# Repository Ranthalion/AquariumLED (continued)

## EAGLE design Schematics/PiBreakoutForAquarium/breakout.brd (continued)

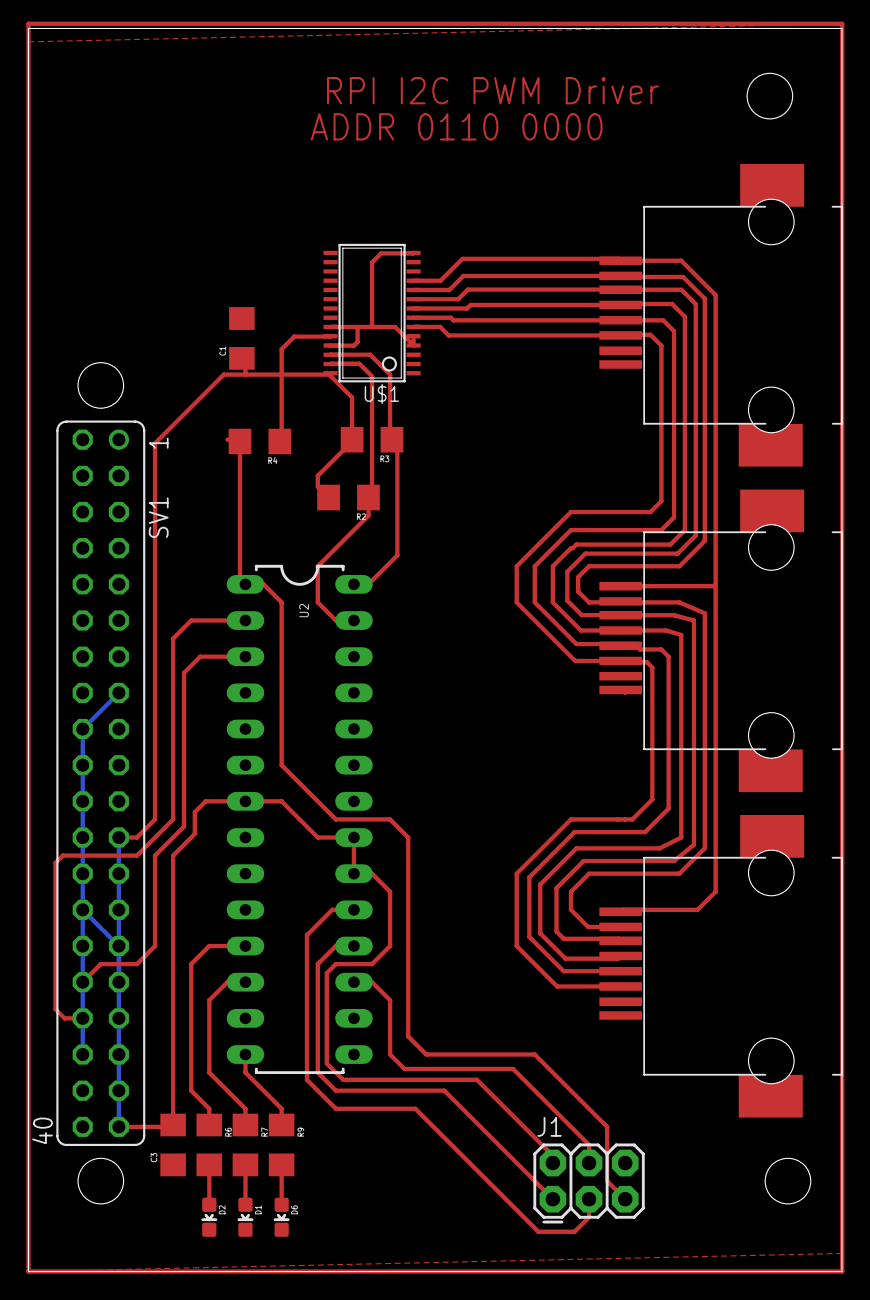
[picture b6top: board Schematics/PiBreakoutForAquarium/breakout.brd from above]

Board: 2 copper layers, 57.1 x 87.3 mm, 18 parts (0 on the bottom side), 22 nets.

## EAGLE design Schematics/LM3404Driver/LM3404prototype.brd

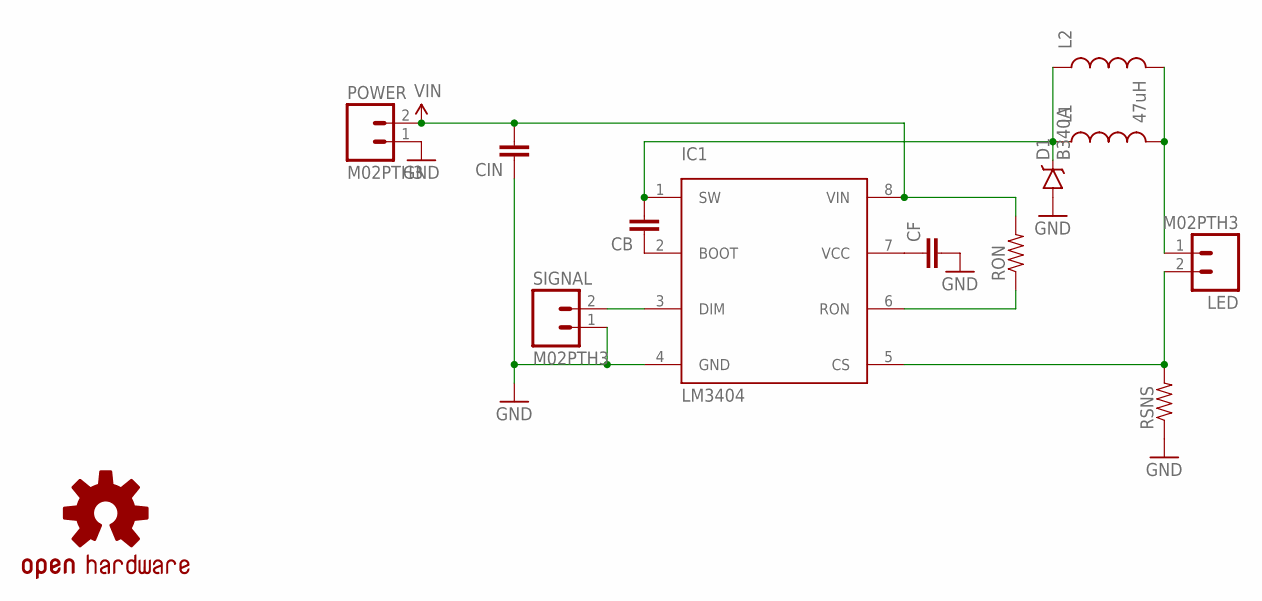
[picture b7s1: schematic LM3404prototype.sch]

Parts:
CB: CAP1206; 1206
CF: CAP1206; 1206
CIN: CAP1206; 1206
D1: B340A; SMA-DIODE
IC1: LM3404; SO8
L1: 47uH; CR75
L2: INDUCTORSDR1105; B82462G
LED: M02PTH3; 1X02_LONGPADS
LOGO1: OSHW-LOGOS; OSHW-LOGO-S
POWER: M02PTH3; 1X02_LONGPADS
RON: RESISTOR1206; 1206
RSNS: RESISTOR1206; 1206
SIGNAL: M02PTH3; 1X02_LONGPADS

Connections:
GND: CF.2, CIN.1, D1.A, IC1.4 (GND), POWER.1, RSNS.1, SIGNAL.1
unnamed: CF.1, IC1.7 (VCC)
unnamed: CB.1, IC1.2 (BOOT)
unnamed: CB.2, D1.C, IC1.1 (SW), L1.P$1 (1), L2.P$1 (1)
unnamed: IC1.5 (CS), LED.2, RSNS.2
unnamed: IC1.6 (RON), RON.1
unnamed: IC1.3 (DIM), SIGNAL.2
unnamed: L1.P$2 (2), L2.P$2 (2), LED.1
VIN: CIN.2, IC1.8 (VIN), POWER.2, RON.2

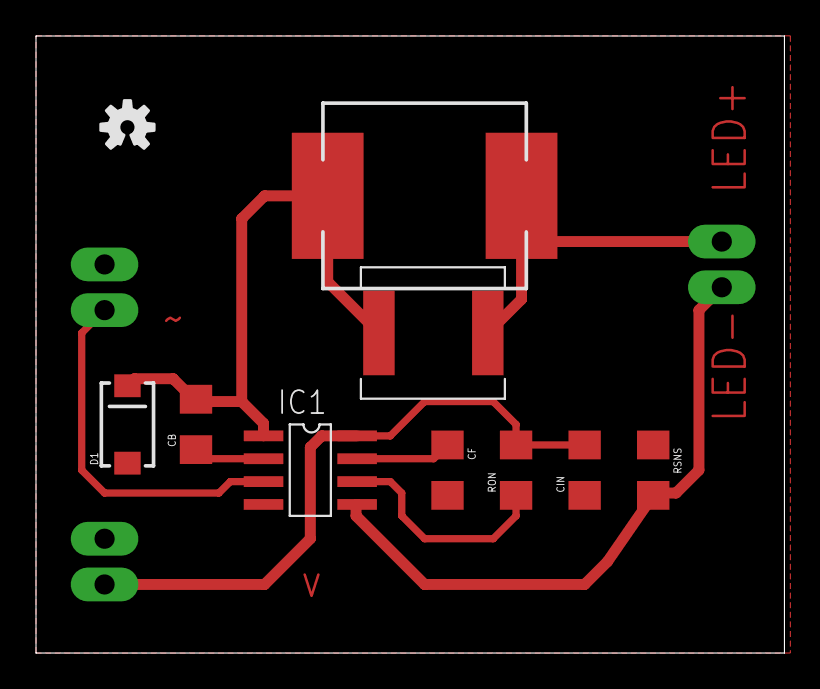
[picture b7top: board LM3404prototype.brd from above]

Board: 2 copper layers, 41.6 x 34.3 mm, 13 parts (0 on the bottom side), 9 nets.

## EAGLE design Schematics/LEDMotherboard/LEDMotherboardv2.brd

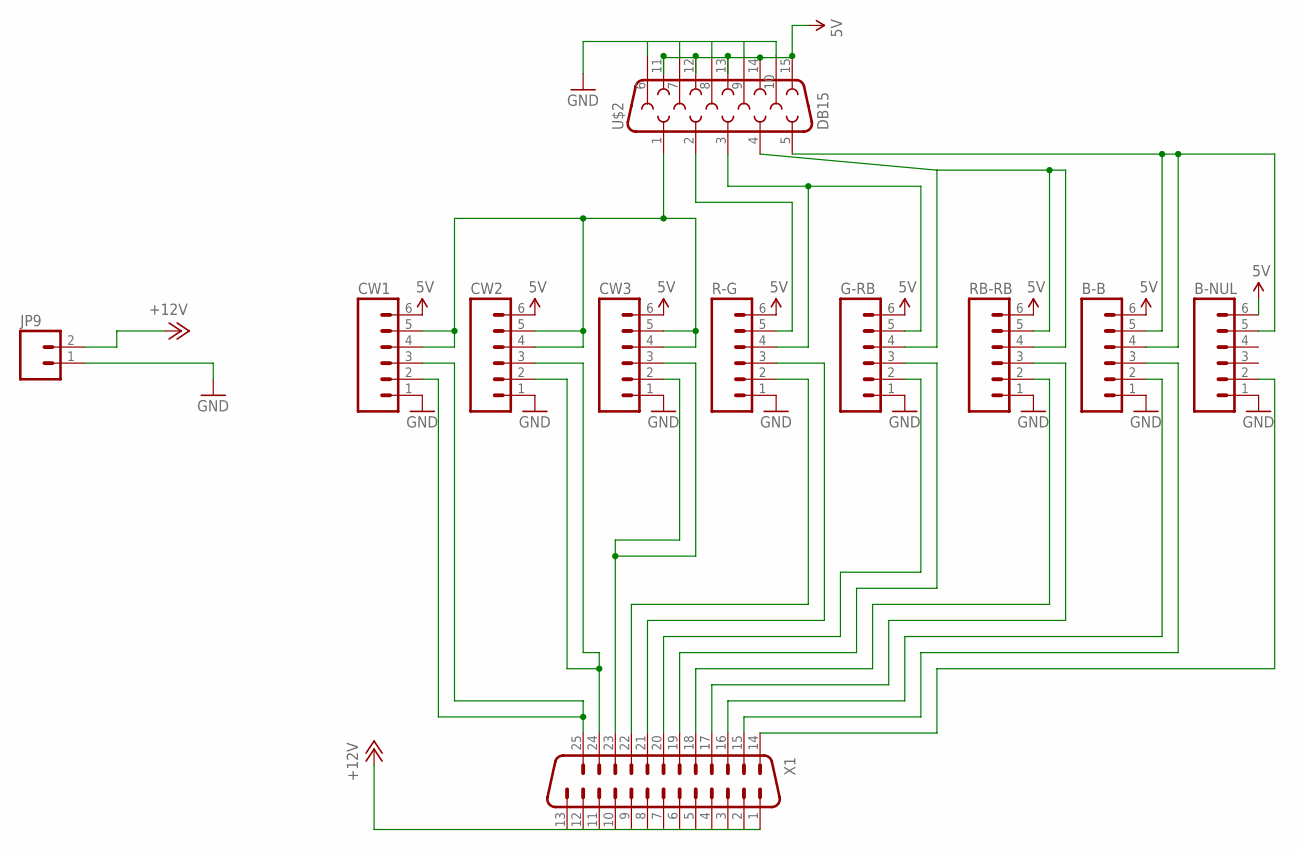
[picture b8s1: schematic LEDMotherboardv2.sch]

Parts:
B-B: M06LOCK_LONGPADS; 1X06_LOCK_LONGPADS
B-NUL: M06LOCK_LONGPADS; 1X06_LOCK_LONGPADS
CW1, CW2, CW3: M06LOCK_LONGPADS; 1X06_LOCK_LONGPADS
G-RB: M06LOCK_LONGPADS; 1X06_LOCK_LONGPADS
JP9: M02; 02P
R-G: M06LOCK_LONGPADS; 1X06_LOCK_LONGPADS
RB-RB: M06LOCK_LONGPADS; 1X06_LOCK_LONGPADS
U$2: DB15
X1: DB25HP; M25HP

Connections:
5V: B-B.6, B-NUL.6, CW1.6, CW2.6, CW3.6, G-RB.6, R-G.6, RB-RB.6, U$2.11, U$2.12, U$2.13, U$2.14, U$2.15
+12V: JP9.2, X1.1, X1.2, X1.3, X1.4, X1.5, X1.6, X1.7, X1.8, X1.9, X1.10, X1.11, X1.12, X1.13
GND: B-B.1, B-NUL.1, CW1.1, CW2.1, CW3.1, G-RB.1, JP9.1, R-G.1, RB-RB.1, U$2.6, U$2.7, U$2.8, U$2.9, U$2.10
unnamed: R-G.5, U$2.2
unnamed: B-B.4, B-B.5, B-NUL.5, U$2.5
unnamed: CW1.4, CW1.5, CW2.4, CW2.5, CW3.4, CW3.5, U$2.1
unnamed: CW2.2, CW2.3, X1.24
unnamed: G-RB.5, R-G.4, U$2.3
unnamed: G-RB.4, RB-RB.4, RB-RB.5, U$2.4
unnamed: CW3.2, CW3.3, X1.23
unnamed: R-G.3, X1.21
unnamed: R-G.2, X1.22
unnamed: G-RB.2, X1.20
unnamed: CW1.2, CW1.3, X1.25
unnamed: G-RB.3, X1.19
unnamed: RB-RB.2, X1.18
unnamed: RB-RB.3, X1.17
unnamed: B-B.2, X1.16
unnamed: B-B.3, X1.15
unnamed: B-NUL.2, X1.14

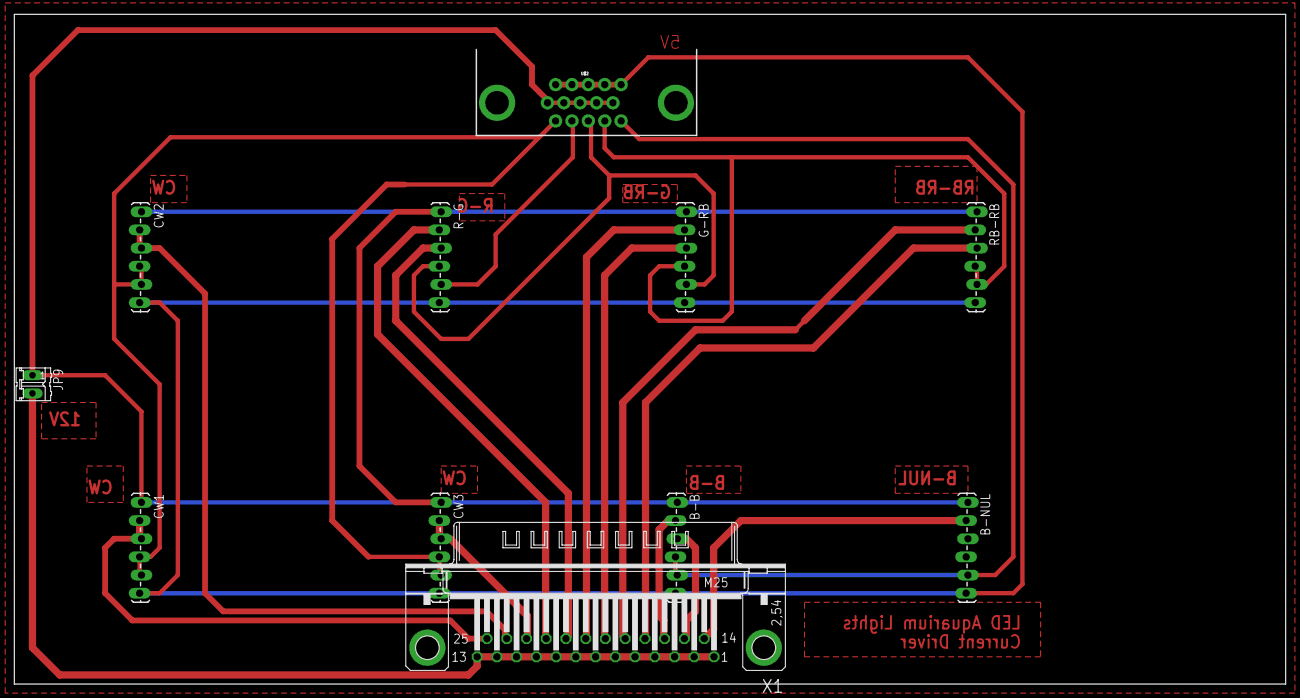
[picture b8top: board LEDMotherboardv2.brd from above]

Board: 2 copper layers, 177.8 x 93.7 mm, 11 parts (0 on the bottom side), 20 nets.

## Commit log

2013-11-09 Adding schematics
2013-11-22 Initial web app check in with Locomotive.
2013-11-22 Adding startup script
2013-11-22 Adding instructions in readme
2013-12-01 Adding v6 LED driver schematic and web app
2013-12-03 Adding direct control and ajax queuing
2013-12-05 half update to correct visualizer
2013-12-06 Visualizer bugs fixed by correcting editor
2013-12-07 Updating PWM Driver to handle bad data
2013-12-11 Adding DAL, but need to fix Direct update.
2013-12-12 Resolving conflict
2013-12-13 Fixing serialization errors
2013-12-13 Updating Channel Editor for direct control
2014-02-15 Various Updates
2014-03-04 LED Motherboard
2014-12-28 Hooking up schedule persistence
2014-12-29 Add circuit for switching design based on LM3404
2015-01-01 a bit of clean up
2015-01-01 Schedule js refactoring
2015-07-25 moving to sails and PCA9685 driver
2015-08-03 PCA9685 bug fixes and emulation. Add fade on and off scripts.
2015-08-11 uhhh
2016-03-20 Add Pi Breakout board
2016-04-06 New AVR based firmware
2016-04-11 Blendini app update to retrieve and save channel settings
2016-04-12 Tweaks to save settings
    Make it look better using tiles, implement auto save, and improved
    responsive layout.
2016-04-13 Adding direct control sliders
2016-04-17 Channel Setting moved to directive
2016-04-17 adding directive
2016-04-17 fix text color on channel editor
2016-04-19 refactor schedule to have multiple transitions
2016-04-22 Add cron and schedule sync
2016-04-22 TODO update
2016-04-25 add serial communication to light scheduler
2016-04-28 Update power driver board to smt RJ45 and correct ground pins
2016-04-29 System State added to Blendini and serial protocol tweaks to firmware
2016-05-02 Serial emulation and direct control
2016-05-04 Bug fixes getting current values from LED driver
2016-05-07 Schedule/Direct control bug fix
2016-08-09 Moving to angular and adding PCA9685 reset to firmware
2016-08-24 Refactor angular code to something reasonable.
2016-08-24 add font awesome to prod build
2016-09-18 Moving some more stuff to angular
2016-09-25 ATMEGA328PB Hat
2016-09-28 LEDs and serial echo on ATMEGA328PB
2016-09-30 Serial echo
2016-10-01 Interrupt based UART
2016-10-01 command buffer fixed
2016-10-02 PWM Initialization
2016-10-03 PWM commands and test scripts
2016-10-05 set and read channel commands
2016-10-05 Fade timer set up
2016-10-05 Bugged up fade
2016-10-05 Fix fade bug and updated test scripts
2016-10-06 Disable PWM when channel set to 0
2016-10-06 Removing outdated code and projects
2016-10-06 Update Blendini to use 8 bit values and new serial commands
2016-10-08 Bug Fixes
2017-01-22 hardware updates
2017-01-29 New signal conditioner - split channels
2017-02-02 Add pull down and update divider
2017-02-20 New breakout with PH, temp, and moisture sensor
2017-02-20 ignore temp eagle files
2017-03-06 Temperature and PH firmware
2017-03-11 Log PH and temperature
2017-03-24 Adding AWS for persistence and calibration
2017-03-31 AWS integration
2017-04-30 enclosure
2017-05-28 enclosure and debugging updates
2018-08-04 Backlink to CADLAB.io has been added.
